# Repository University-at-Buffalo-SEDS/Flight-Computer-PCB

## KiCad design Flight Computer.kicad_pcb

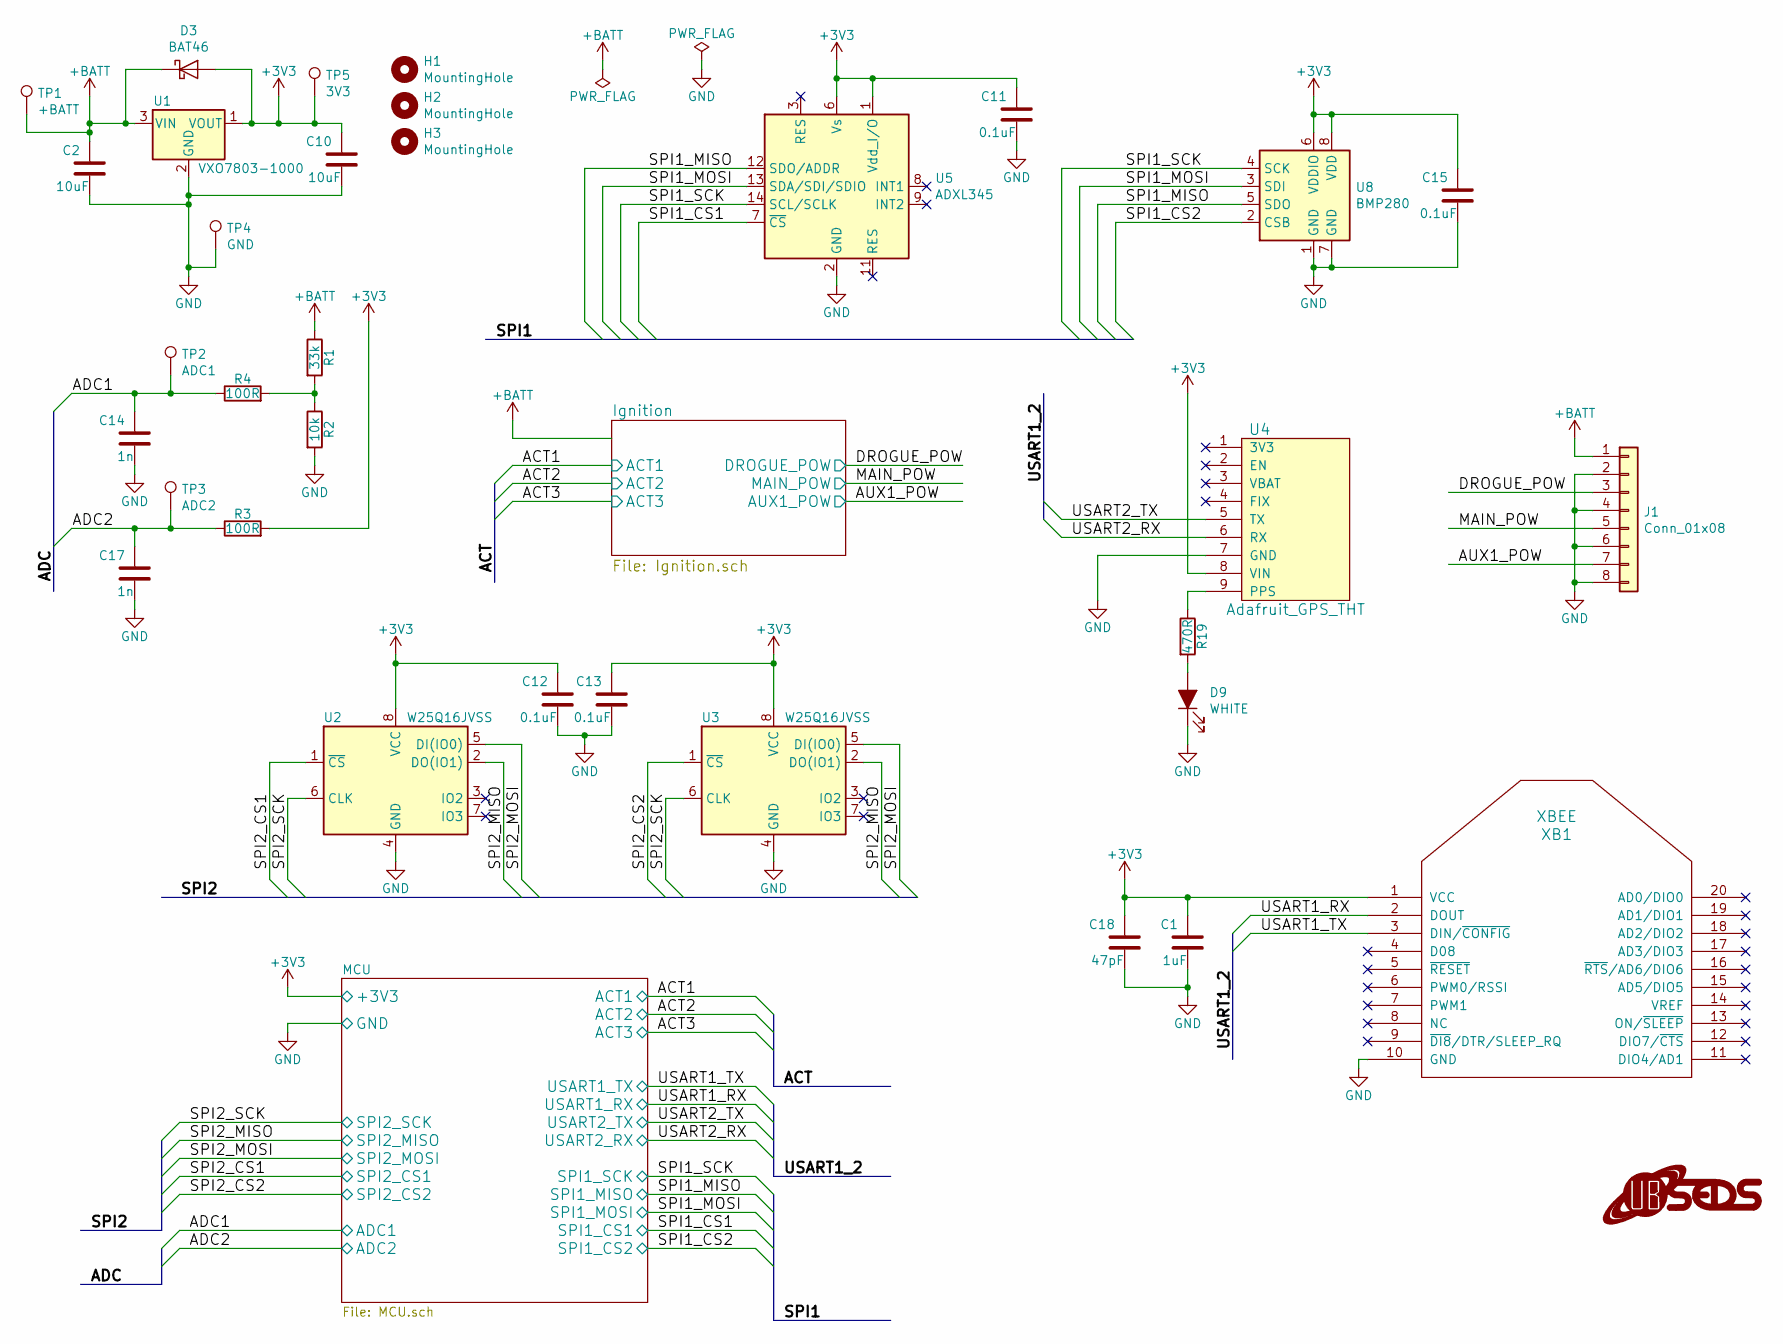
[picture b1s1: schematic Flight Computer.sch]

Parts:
C1: 1uF; C_0603_1608Metric_Pad1.05x0.95mm_HandSolder
C2, C10: 10uF; C_1206_3216Metric_Pad1.42x1.75mm_HandSolder
C11, C12, C13, C15: 0.1uF; C_0603_1608Metric_Pad1.05x0.95mm_HandSolder
C14, C17: 1n; C_0603_1608Metric_Pad1.05x0.95mm_HandSolder
C18: 47pF; C_0603_1608Metric_Pad1.05x0.95mm_HandSolder
D3: BAT46; D_SOD-123
D9: WHITE; LED_0603_1608Metric_Pad1.05x0.95mm_HandSolder
G1: LOGO; SEDS_logo_soldermask
H1, H2, H3: MountingHole; MountingHole_2.5mm
J1: Conn_01x08; PinHeader_1x08_P2.54mm_Vertical
R1: 33k; R_0603_1608Metric_Pad1.05x0.95mm_HandSolder
R2: 10k; R_0603_1608Metric_Pad1.05x0.95mm_HandSolder
R3, R4: 100R; R_0603_1608Metric_Pad1.05x0.95mm_HandSolder
R19: 470R; R_0603_1608Metric_Pad1.05x0.95mm_HandSolder
TP1: +BATT; TestPoint_Pad_D1.0mm
TP2: ADC1; TestPoint_Pad_D1.0mm
TP3: ADC2; TestPoint_Pad_D1.0mm
TP4: GND; TestPoint_Pad_D1.0mm
TP5: 3V3; TestPoint_Pad_D1.0mm
U1: VXO7803-1000
U2, U3: W25Q16JVSS; SOIC-8_5.23x5.23mm_P1.27mm
U4: Adafruit_GPS_THT
U5: ADXL345; CC-14-1
U8: BMP280; Bosch_LGA-8_2x2.5mm_P0.65mm_ClockwisePinNumbering
XB1: XBEE; XBEE_PRO_PTH

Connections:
+3V3: C1.2, C10.2, C11.2, C12.2, C13.2, C15.2, C18.2, D3.2 (A), R3.2, TP5.1, U1.1 (VOUT), U2.8 (VCC), U3.8 (VCC), U4.8 (VIN), U5.1 (Vdd_I/O), U5.6 (Vs), U8.6 (VDDIO), U8.8 (VDD), XB1.1 (VCC); also elsewhere on the board
+BATT: C2.2, D3.1 (K), J1.1, R1.1, TP1.1, U1.3 (VIN); also elsewhere on the board
/ADC1: C14.2, R4.1, TP2.1; also elsewhere on the board
/ADC2: C17.2, R3.1, TP3.1; also elsewhere on the board
/AUX1_POW: J1.7; also elsewhere on the board
/DROGUE_POW: J1.3; also elsewhere on the board
/MAIN_POW: J1.5; also elsewhere on the board
/SPI1_CS1: U5.7 (~CS); also elsewhere on the board
/SPI1_CS2: U8.2 (CSB); also elsewhere on the board
/SPI1_MISO: U5.12 (SDO/ADDR), U8.5 (SDO); also elsewhere on the board
/SPI1_MOSI: U5.13 (SDA/SDI/SDIO), U8.3 (SDI); also elsewhere on the board
/SPI1_SCK: U5.14 (SCL/SCLK), U8.4 (SCK); also elsewhere on the board
/SPI2_CS1: U2.1 (~CS); also elsewhere on the board
/SPI2_CS2: U3.1 (~CS); also elsewhere on the board
/SPI2_MISO: U2.2 (DO(IO1)), U3.2 (DO(IO1)); also elsewhere on the board
/SPI2_MOSI: U2.5 (DI(IO0)), U3.5 (DI(IO0)); also elsewhere on the board
/SPI2_SCK: U2.6 (CLK), U3.6 (CLK); also elsewhere on the board
/USART1_RX: XB1.2 (DOUT); also elsewhere on the board
/USART1_TX: XB1.3 (DIN/~CONFIG); also elsewhere on the board
/USART2_RX: U4.6 (RX); also elsewhere on the board
/USART2_TX: U4.5 (TX); also elsewhere on the board
GND: C1.1, C2.1, C10.1, C11.1, C12.1, C13.1, C14.1, C15.1, C17.1, C18.1, D9.1 (K), J1.2, J1.4, J1.6, J1.8, R2.2, TP4.1, U1.2 (GND), U2.4 (GND), U3.4 (GND), U4.7 (GND), U5.2 (GND), U5.4 (GND), U5.5 (GND), U8.1 (GND), U8.7 (GND), XB1.10 (GND); also elsewhere on the board
unnamed: D9.2 (A), R19.2
unnamed: R1.2, R2.1, R4.2
unnamed: R19.1, U4.9 (PPS)

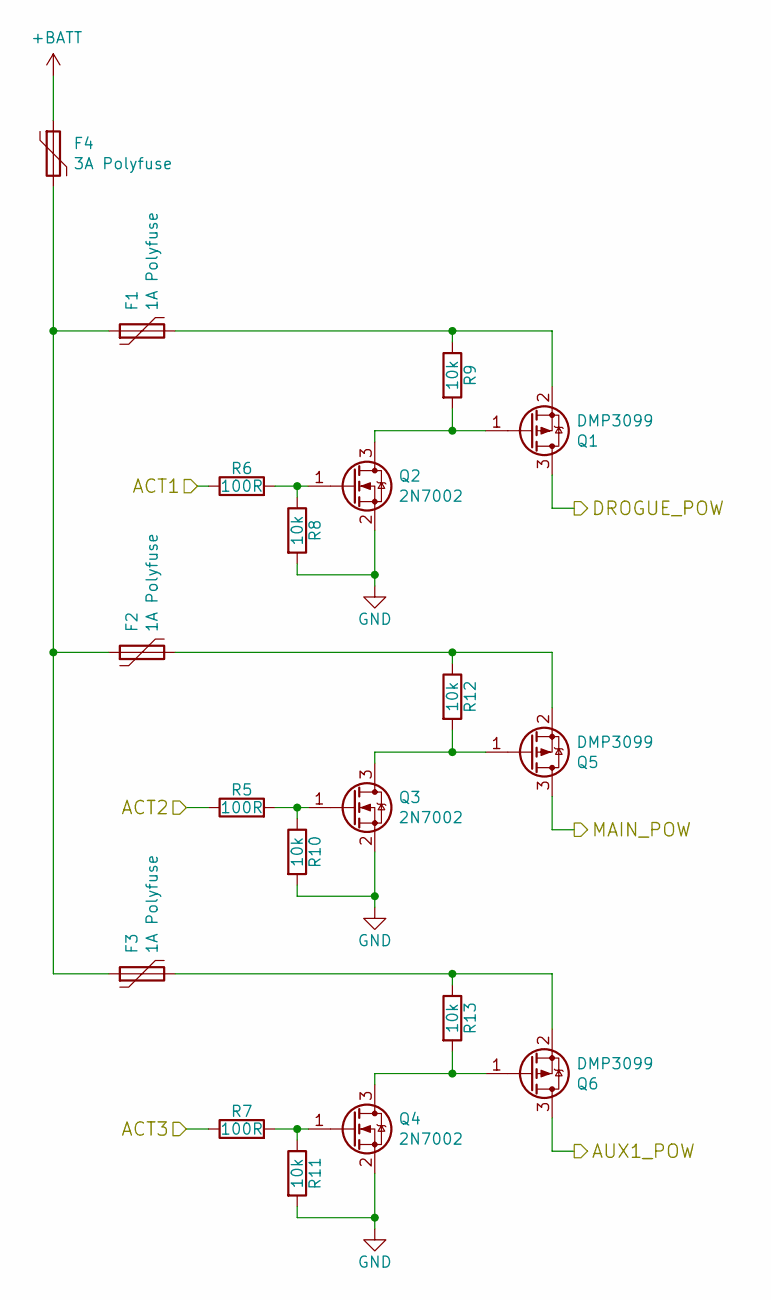
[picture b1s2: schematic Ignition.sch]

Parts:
F1, F2, F3: 1A Polyfuse; Fuse_1206_3216Metric_Pad1.42x1.75mm_HandSolder
F4: 3A Polyfuse; Fuse_1206_3216Metric_Pad1.42x1.75mm_HandSolder
Q1, Q5, Q6: DMP3099; SOT-23
Q2, Q3, Q4: 2N7002; SOT-23
R5, R6, R7: 100R; R_0603_1608Metric_Pad1.05x0.95mm_HandSolder
R8, R9, R10, R11, R12, R13: 10k; R_0603_1608Metric_Pad1.05x0.95mm_HandSolder

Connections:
+BATT: F4.1; also elsewhere on the board
/ACT1: R6.1; also elsewhere on the board
/ACT2: R5.1; also elsewhere on the board
/ACT3: R7.1; also elsewhere on the board
/AUX1_POW: Q6.3 (D); also elsewhere on the board
/DROGUE_POW: Q1.3 (D); also elsewhere on the board
/MAIN_POW: Q5.3 (D); also elsewhere on the board
GND: Q2.2 (S), Q3.2 (S), Q4.2 (S), R8.2, R10.2, R11.2; also elsewhere on the board
unnamed: F1.1, F2.1, F3.1, F4.2
unnamed: F1.2, Q1.2 (S), R9.1
unnamed: F2.2, Q5.2 (S), R12.1
unnamed: F3.2, Q6.2 (S), R13.1
unnamed: Q1.1 (G), Q2.3 (D), R9.2
unnamed: Q2.1 (G), R6.2, R8.1
unnamed: Q3.1 (G), R5.2, R10.1
unnamed: Q3.3 (D), Q5.1 (G), R12.2
unnamed: Q4.1 (G), R7.2, R11.1
unnamed: Q4.3 (D), Q6.1 (G), R13.2

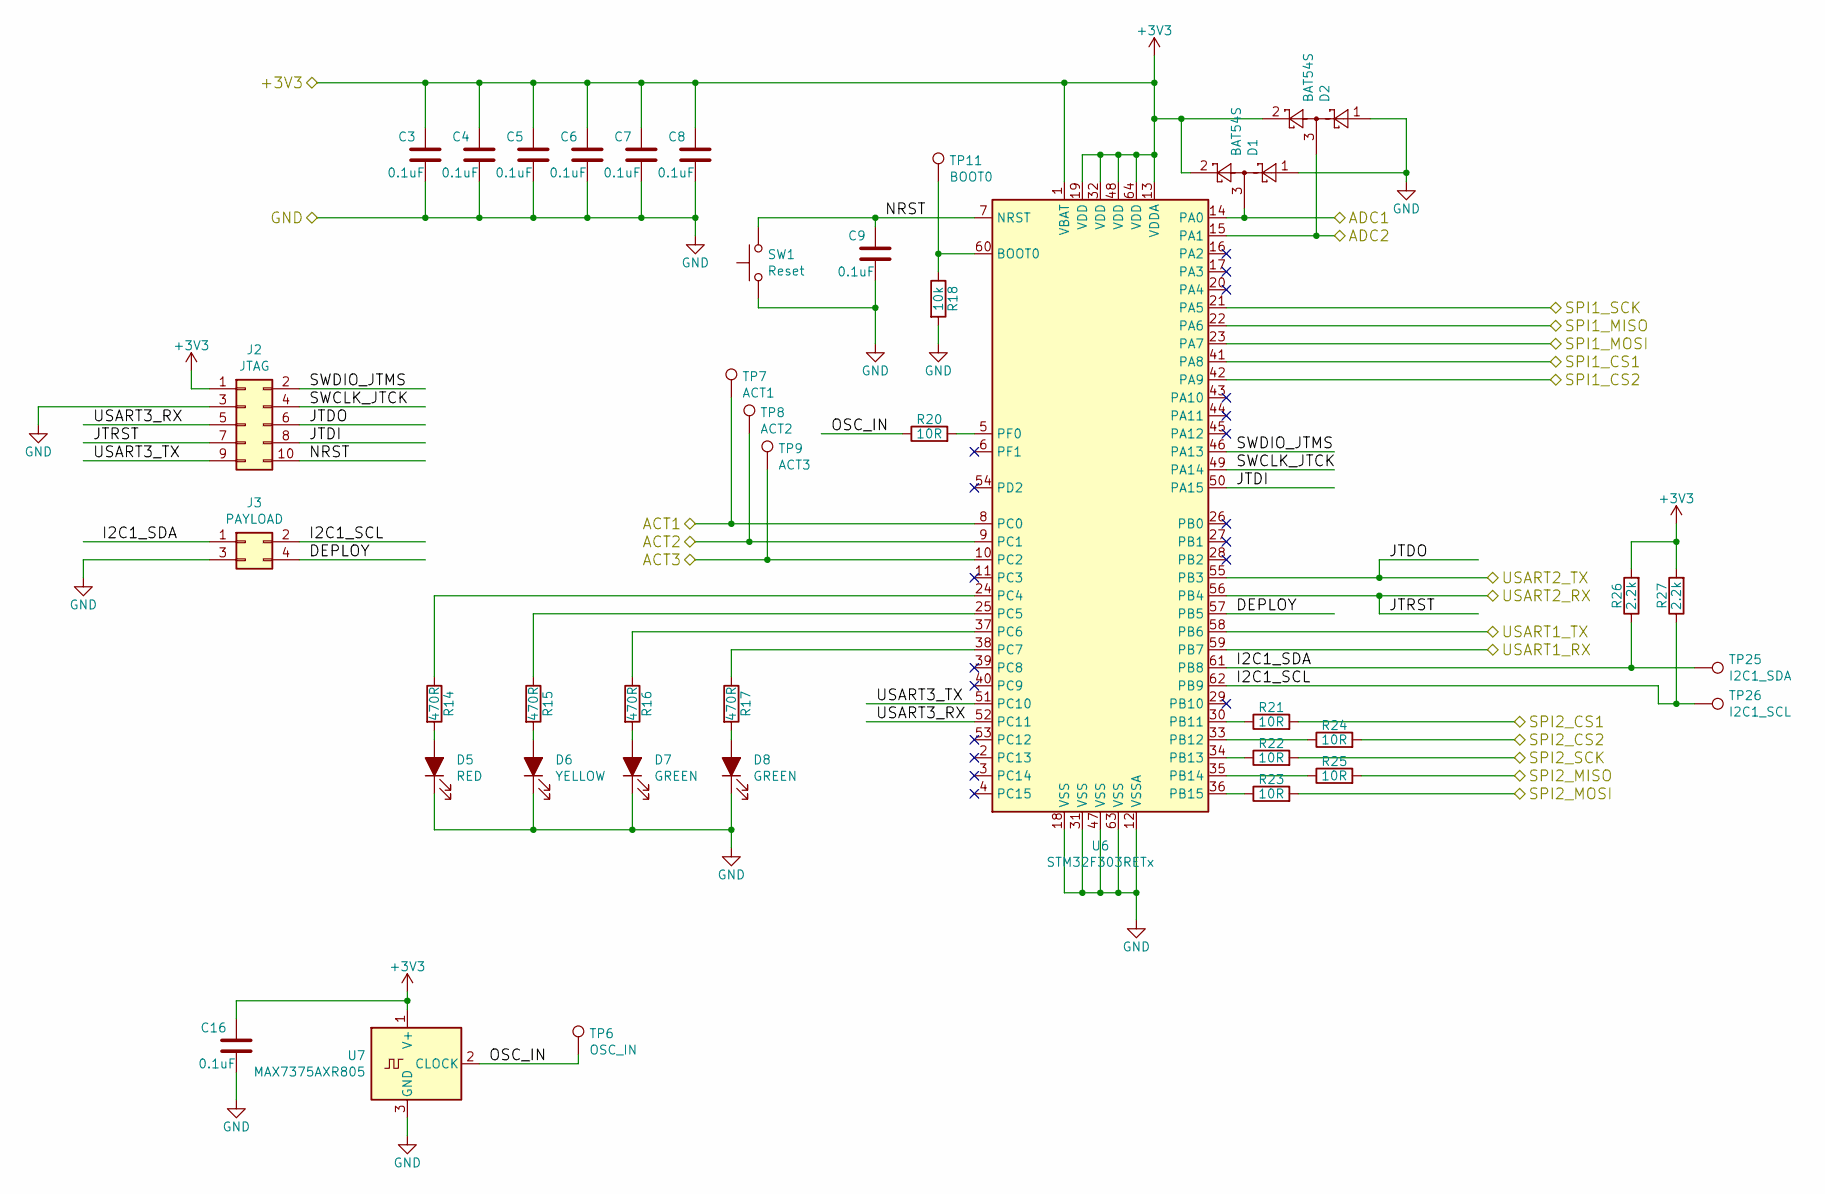
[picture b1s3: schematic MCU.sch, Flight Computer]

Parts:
C3, C4, C5, C6, C7, C8, C9, C16: 0.1uF; C_0603_1608Metric_Pad1.05x0.95mm_HandSolder
D1, D2: BAT54S; SOT-23
D5: RED; LED_0603_1608Metric_Pad1.05x0.95mm_HandSolder
D6: YELLOW; LED_0603_1608Metric_Pad1.05x0.95mm_HandSolder
D7, D8: GREEN; LED_0603_1608Metric_Pad1.05x0.95mm_HandSolder
J2: JTAG; PinHeader_2x05_P1.27mm_Vertical_SMD
J3: PAYLOAD; PinHeader_2x02_P1.27mm_Vertical
R14, R15, R16, R17: 470R; R_0603_1608Metric_Pad1.05x0.95mm_HandSolder
R18: 10k; R_0603_1608Metric_Pad1.05x0.95mm_HandSolder
R20, R21, R22, R23, R24, R25: 10R; R_0603_1608Metric_Pad1.05x0.95mm_HandSolder
R26, R27: 2.2k; R_0603_1608Metric_Pad1.05x0.95mm_HandSolder
SW1: Reset; SW_Push_1P1T_NO_CK_KMR2
TP6: OSC_IN; TestPoint_Pad_D1.0mm
TP7: ACT1; TestPoint_Pad_D1.0mm
TP8: ACT2; TestPoint_Pad_D1.0mm
TP9: ACT3; TestPoint_Pad_D1.0mm
TP11: BOOT0; TestPoint_Pad_D1.0mm
TP25: I2C1_SDA; TestPoint_Pad_D1.0mm
TP26: I2C1_SCL; TestPoint_Pad_D1.0mm
U6: STM32F303RETx; LQFP-64_10x10mm_P0.5mm
U7: MAX7375AXR805; SOT-323_SC-70

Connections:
+3V3: C3.2, C4.2, C5.2, C6.2, C7.2, C8.2, C16.2, D1.2, D2.2, J2.1, R26.2, R27.2, U6.1 (VBAT), U6.13 (VDDA), U6.19 (VDD), U6.32 (VDD), U6.48 (VDD), U6.64 (VDD), U7.1 (V+); also elsewhere on the board
/ACT1: TP7.1, U6.8 (PC0); also elsewhere on the board
/ACT2: TP8.1, U6.9 (PC1); also elsewhere on the board
/ACT3: TP9.1, U6.10 (PC2); also elsewhere on the board
/ADC1: D1.3, U6.14 (PA0); also elsewhere on the board
/ADC2: D2.3, U6.15 (PA1); also elsewhere on the board
/MCU/DEPLOY: J3.4, U6.57 (PB5)
/MCU/I2C1_SCL: J3.2, R27.1, TP26.1, U6.62 (PB9)
/MCU/I2C1_SDA: J3.1, R26.1, TP25.1, U6.61 (PB8)
/MCU/JTDI: J2.8, U6.50 (PA15)
/MCU/NRST: C9.2, J2.10, SW1.2, U6.7 (NRST)
/MCU/OSC_IN: R20.1, TP6.1, U7.2 (CLOCK)
/MCU/SWCLK_JTCK: J2.4, U6.49 (PA14)
/MCU/SWDIO_JTMS: J2.2, U6.46 (PA13)
/MCU/USART3_RX: J2.5, U6.52 (PC11)
/MCU/USART3_TX: J2.9, U6.51 (PC10)
/SPI1_CS1: U6.41 (PA8); also elsewhere on the board
/SPI1_CS2: U6.42 (PA9); also elsewhere on the board
/SPI1_MISO: U6.22 (PA6); also elsewhere on the board
/SPI1_MOSI: U6.23 (PA7); also elsewhere on the board
/SPI1_SCK: U6.21 (PA5); also elsewhere on the board
/SPI2_CS1: R21.2; also elsewhere on the board
/SPI2_CS2: R24.2; also elsewhere on the board
/SPI2_MISO: R25.2; also elsewhere on the board
/SPI2_MOSI: R23.2; also elsewhere on the board
/SPI2_SCK: R22.2; also elsewhere on the board
/USART1_RX: U6.59 (PB7); also elsewhere on the board
/USART1_TX: U6.58 (PB6); also elsewhere on the board
/USART2_RX: J2.7, U6.56 (PB4); also elsewhere on the board
/USART2_TX: J2.6, U6.55 (PB3); also elsewhere on the board
GND: C3.1, C4.1, C5.1, C6.1, C7.1, C8.1, C9.1, C16.1, D1.1, D2.1, D5.1 (K), D6.1 (K), D7.1 (K), D8.1 (K), J2.3, J3.3, R18.2, SW1.1, U6.12 (VSSA), U6.18 (VSS), U6.31 (VSS), U6.47 (VSS), U6.63 (VSS), U7.3 (GND); also elsewhere on the board
unnamed: D5.2 (A), R14.2
unnamed: D6.2 (A), R15.2
unnamed: D7.2 (A), R16.2
unnamed: D8.2 (A), R17.2
unnamed: R14.1, U6.24 (PC4)
unnamed: R15.1, U6.25 (PC5)
unnamed: R16.1, U6.37 (PC6)
unnamed: R17.1, U6.38 (PC7)
unnamed: R18.1, TP11.1, U6.60 (BOOT0)
unnamed: R20.2, U6.5 (PF0)
unnamed: R21.1, U6.30 (PB11)
unnamed: R22.1, U6.34 (PB13)
unnamed: R23.1, U6.36 (PB15)
unnamed: R24.1, U6.33 (PB12)
unnamed: R25.1, U6.35 (PB14)

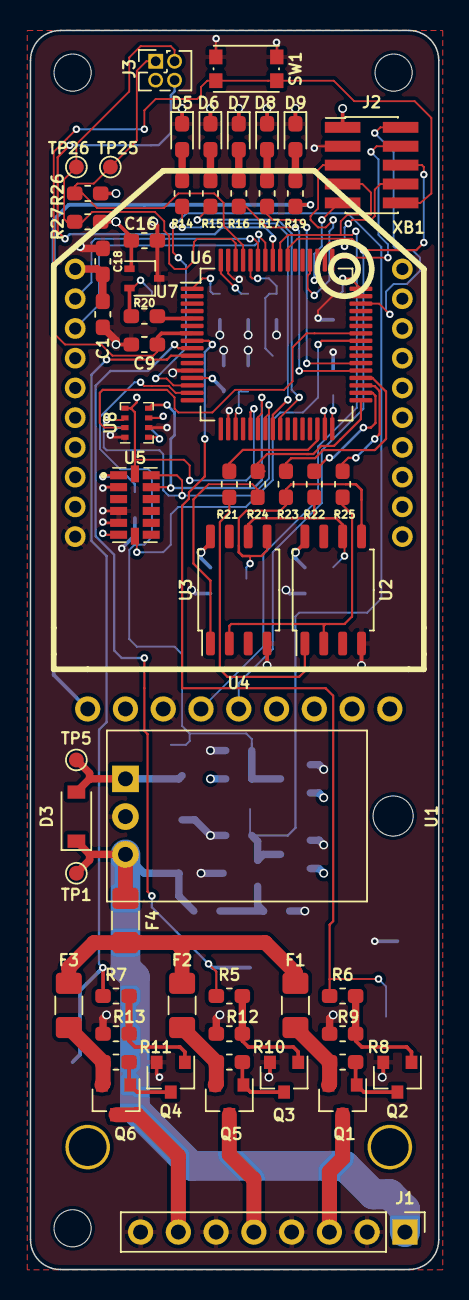
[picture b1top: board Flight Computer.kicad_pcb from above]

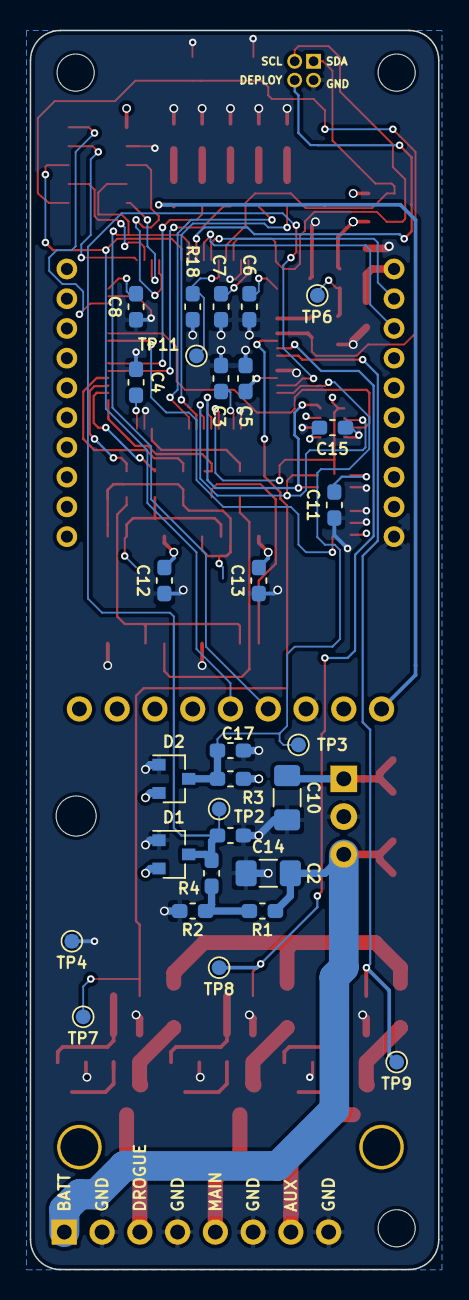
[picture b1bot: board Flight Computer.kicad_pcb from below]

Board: 4 copper layers, 27.5 x 83.3 mm, 92 parts (30 on the bottom side), 63 nets.

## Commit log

2019-12-11 New V2 integrated flight computer schematic Moved MCU to its own sheet Added datasheets Added KiCAD footprint submodule
2019-12-13 Added JTAG and BOOT connectors to MCU Moved I2C1 pins
2019-12-13 Updated pinmap
2019-12-20 New pyro transistors New IO connector Changed SPI pins
2019-12-24 Starting to fix ERC errors
2019-12-24 Fixed most ERC errors
2020-01-04 Removed redundant ADC protection diodes Basic PCB component layout
2020-01-07 Renamed some components?
2020-01-13 Fixed .gitmodules (host-agnostic) Added bypass caps Added NMOS to ignition sheet Added current-limiting resistors Fixed 3V3 ADC input
2020-01-13 Add external oscillator Add BOOT0 pulldown Remove NRST external pullup Add test LEDs Smaller JTAG connector
2020-01-13 Annotated schematic Added 2N7002 packages Updated PCB
2020-01-13 All ERC errors gone
2020-01-13 GPS module power fixed
2020-01-13 Annotated schematic
2020-01-13 Updated pinmap Added USART3 for external communication
2020-01-14 Cleaned up libraries Changed ADXL345 footprint
2020-01-14 Adding test points
2020-01-14 Finished adding test points Schematic annotated
2020-01-17 Added 10R series termination resistors to high-speed digital lines Added reverse-power protection diode Added ADC filter capacitors Added I2C pullups Added individual polyfuses to pyro drivers Change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
2020-01-19 Preliminary component placement
2020-01-21 Much more compact component placement Some routing done
2020-01-29 Routing complete Removed some test points (couldn't easily place)
2020-02-04 Fixed silk Fixed JTAG Added PAYLOAD connector with I2C
2020-02-05 Add pin labels to silkscreen
2020-02-22 Increase clearance of trace to BOOT0 pin
